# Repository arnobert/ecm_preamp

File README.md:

# Preamp / power supply for ECM microphones, e.g. DPA 4061

## TBD: audio measurements

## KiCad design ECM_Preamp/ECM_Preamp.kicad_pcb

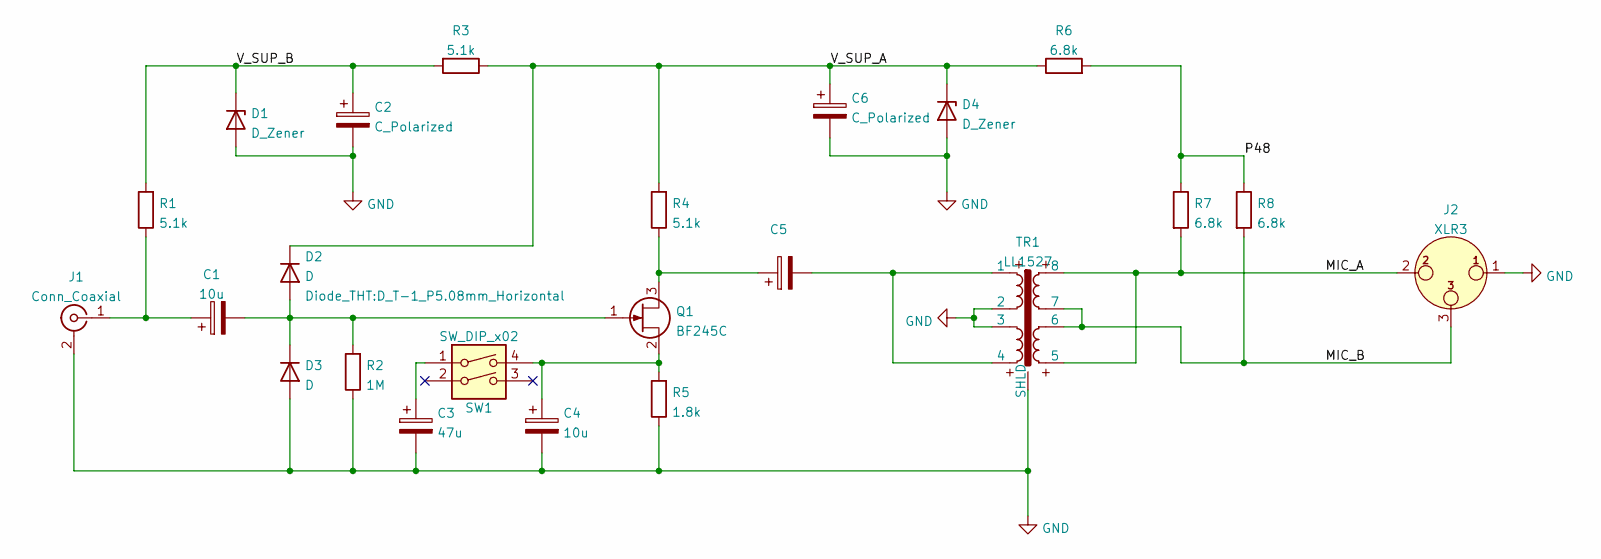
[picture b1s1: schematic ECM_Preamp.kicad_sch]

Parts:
C1, C4: 10u; CP_Radial_D5.0mm_P2.50mm
C2, C6: C_Polarized; CP_Radial_D5.0mm_P2.50mm
C3: 47u; CP_Radial_D5.0mm_P2.50mm
C5: (no value)
D1, D4: D_Zener; D_A-405_P7.62mm_Horizontal
D2, D3: D; D_T-1_P5.08mm_Horizontal
J1: Conn_Coaxial; SMA_Amphenol_132134_Vertical
J2: XLR3; Jack_XLR_Neutrik_NC3FAAH-0_Horizontal
Q1: BF245C; TO-92_Inline
R1, R3, R4: 5.1k; R_Axial_DIN0204_L3.6mm_D1.6mm_P7.62mm_Horizontal
R2: 1M; R_Axial_DIN0204_L3.6mm_D1.6mm_P7.62mm_Horizontal
R5: 1.8k; R_Axial_DIN0204_L3.6mm_D1.6mm_P7.62mm_Horizontal
R6, R7, R8: 6.8k; R_Axial_DIN0204_L3.6mm_D1.6mm_P7.62mm_Horizontal
SW1: SW_DIP_x02; DIP-4_W7.62mm
TR1: LL1527; Transformer_Microphone_Lundahl_LL1527

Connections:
/MIC_A: J2.2, R7.2, TR1.5, TR1.8
/MIC_B: J2.3, R8.2, TR1.6, TR1.7
/P48: R6.2, R7.1, R8.1
/V_SUP_A: C6.1, D2.1 (K), D4.1 (K), R3.1, R4.2, R6.1
/V_SUP_B: C2.1, D1.1 (K), R1.2, R3.2
GND: C2.2, C3.2, C4.2, C6.2, D1.2 (A), D3.2 (A), D4.2 (A), J1.2 (Ext), J2.1, R2.1, R5.1, TR1.2, TR1.3, TR1.9 (SHLD)
unnamed: C1.1, J1.1 (In), R1.1
unnamed: C1.2, D2.2 (A), D3.1 (K), Q1.1 (G), R2.2
unnamed: C3.1, SW1.1
unnamed: C4.1, Q1.2 (S), R5.2, SW1.4
unnamed: C5.1, Q1.3 (D), R4.1
unnamed: C5.2, TR1.1, TR1.4

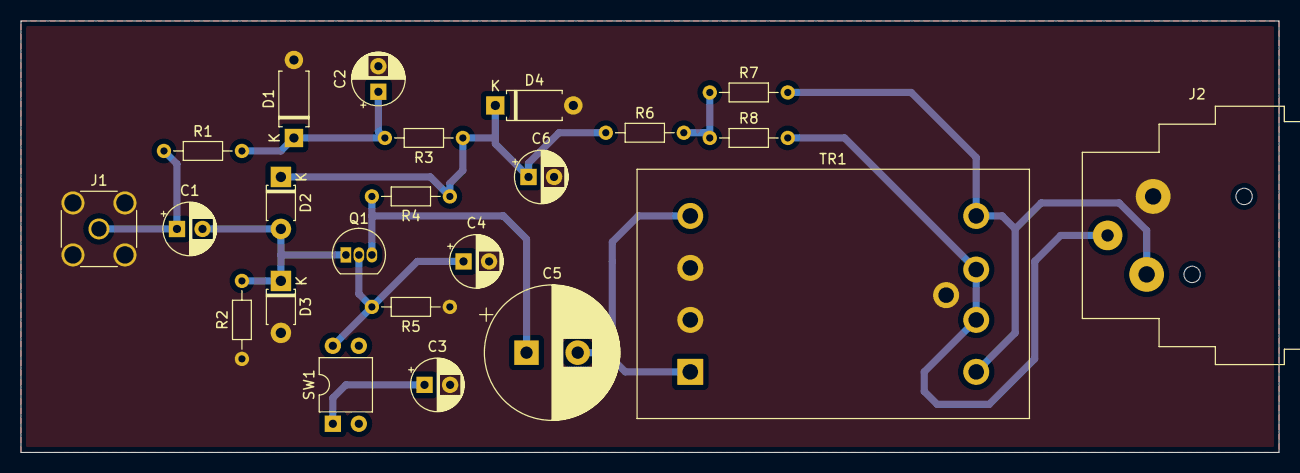
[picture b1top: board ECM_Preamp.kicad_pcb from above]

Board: 2 copper layers, 122.9 x 42.2 mm, 23 parts (0 on the bottom side), 12 nets.

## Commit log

2022-01-23 Added sim
2022-01-23 Updated gitignore
2022-01-23 REV 0
2022-05-05 sim updated, C_pol updated
2022-05-05 Updated component values
2022-05-05 Clean up
